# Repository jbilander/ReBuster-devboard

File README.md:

# ReBuster-devboard
A development board for ReBuster

***

<br />

<br />

<br />

***

***

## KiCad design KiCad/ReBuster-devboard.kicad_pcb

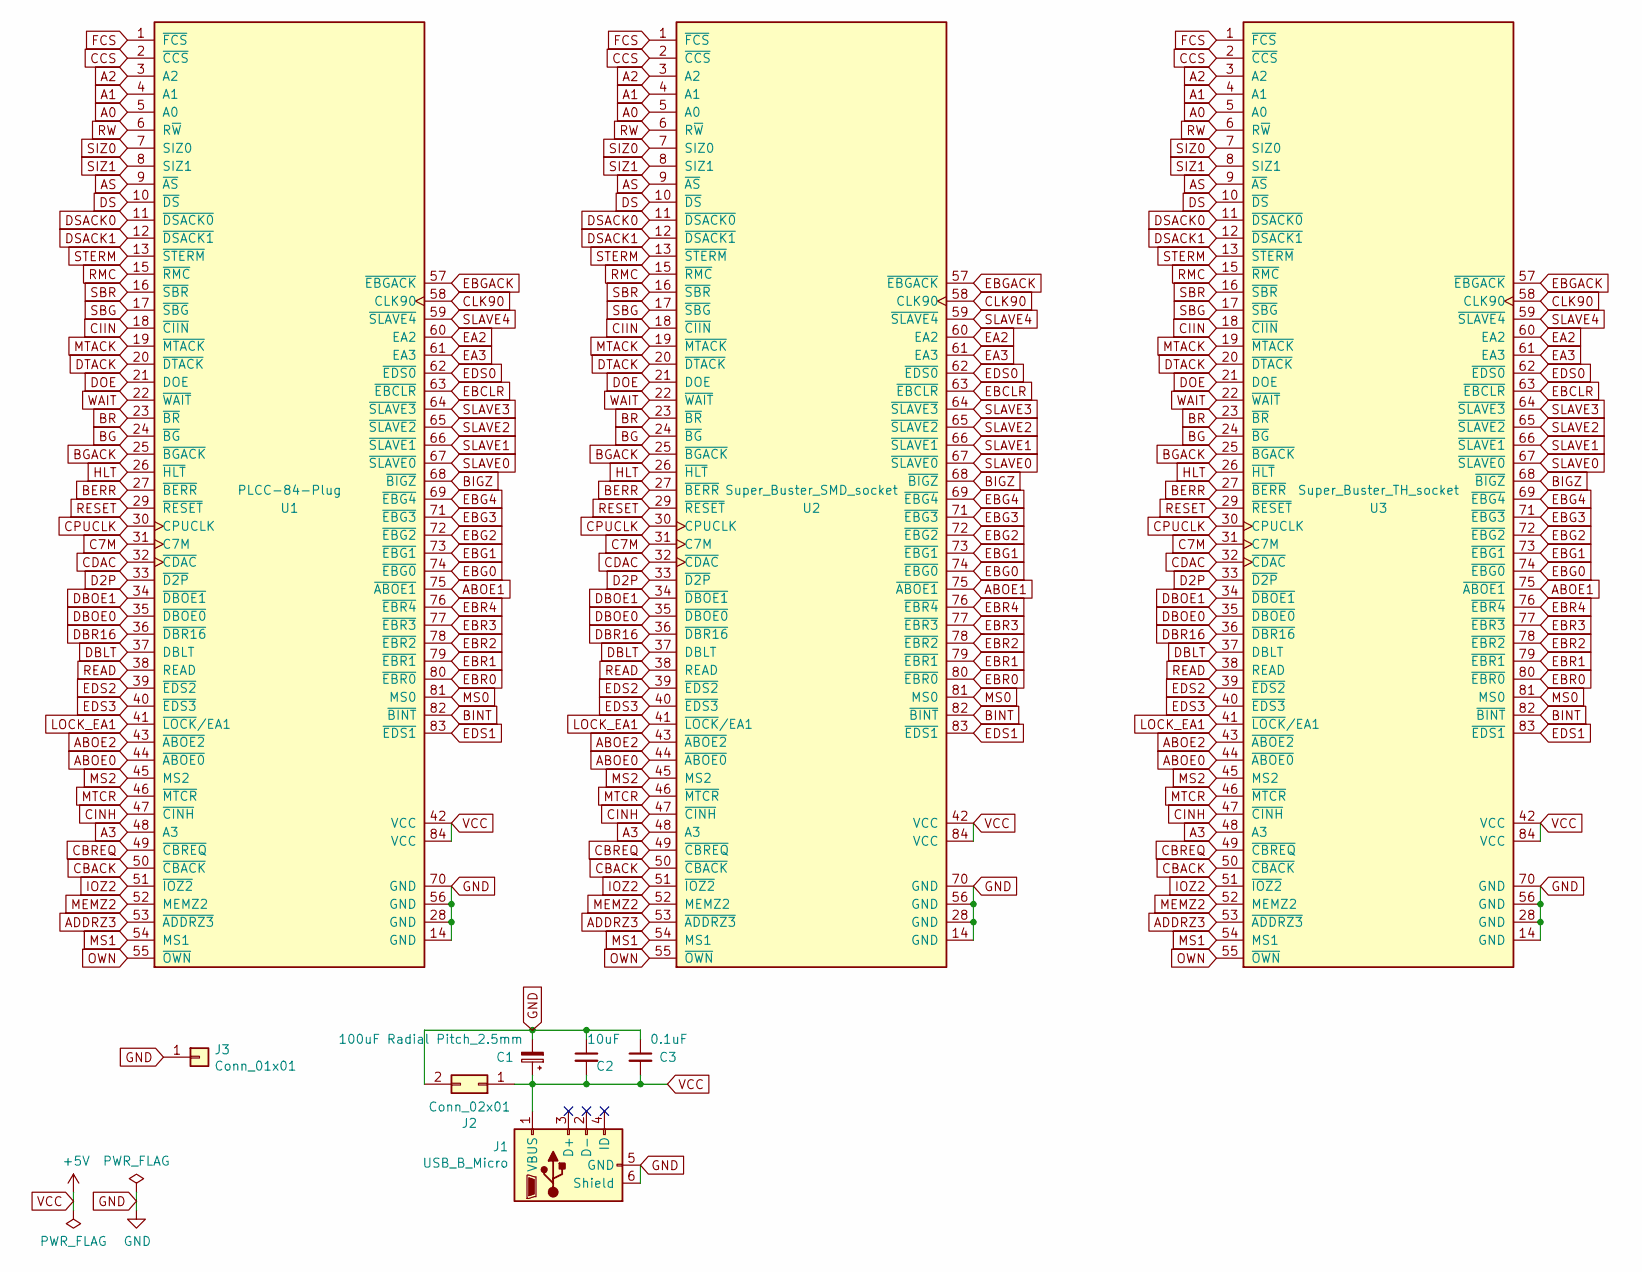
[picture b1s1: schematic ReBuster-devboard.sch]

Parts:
C1: 100uF Radial Pitch_2.5mm; CP_Radial_D5.0mm_P2.50mm
C2: 10uF; C_1206_3216Metric_Pad1.33x1.80mm_HandSolder
C3: 0.1uF; C_0805_2012Metric_Pad1.18x1.45mm_HandSolder
J1: USB_B_Micro; USB_Micro-B_Unknown_5s_SMT
J2: Conn_02x01; PinHeader_2x01_P2.54mm_Vertical
J3: Conn_01x01; MountingHole_3.2mm_M3_Pad_Via
U1: PLCC-84-Plug; PLCC-84_Plug_P1.27mm_mirrored
U2: Super_Buster_SMD_socket; PLCC-84_SMD-Socket_TH_modded
U3: Super_Buster_TH_socket; PLCC-84_THT-Socket

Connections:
A0: U1.5 (A0), U2.5 (A0), U3.5 (A0)
A1: U1.4 (A1), U2.4 (A1), U3.4 (A1)
A2: U1.3 (A2), U2.3 (A2), U3.3 (A2)
A3: U1.48 (A3), U2.48 (A3), U3.48 (A3)
ABOE0: U1.44 (~ABOE0), U2.44 (~ABOE0), U3.44 (~ABOE0)
ABOE1: U1.75 (~ABOE1), U2.75 (~ABOE1), U3.75 (~ABOE1)
ABOE2: U1.43 (~ABOE2), U2.43 (~ABOE2), U3.43 (~ABOE2)
ADDRZ3: U1.53 (~ADDRZ3), U2.53 (~ADDRZ3), U3.53 (~ADDRZ3)
AS: U1.9 (~AS), U2.9 (~AS), U3.9 (~AS)
BERR: U1.27 (~BERR), U2.27 (~BERR), U3.27 (~BERR)
BG: U1.24 (~BG), U2.24 (~BG), U3.24 (~BG)
BGACK: U1.25 (~BGACK), U2.25 (~BGACK), U3.25 (~BGACK)
BIGZ: U1.68 (~BIGZ), U2.68 (~BIGZ), U3.68 (~BIGZ)
BINT: U1.82 (~BINT), U2.82 (~BINT), U3.82 (~BINT)
BR: U1.23 (~BR), U2.23 (~BR), U3.23 (~BR)
C7M: U1.31 (C7M), U2.31 (C7M), U3.31 (C7M)
CBACK: U1.50 (~CBACK), U2.50 (~CBACK), U3.50 (~CBACK)
CBREQ: U1.49 (~CBREQ), U2.49 (~CBREQ), U3.49 (~CBREQ)
CCS: U1.2 (~CCS), U2.2 (~CCS), U3.2 (~CCS)
CDAC: U1.32 (~CDAC), U2.32 (~CDAC), U3.32 (~CDAC)
CIIN: U1.18 (~CIIN), U2.18 (~CIIN), U3.18 (~CIIN)
CINH: U1.47 (~CINH), U2.47 (~CINH), U3.47 (~CINH)
CLK90: U1.58 (CLK90), U2.58 (CLK90), U3.58 (CLK90)
CPUCLK: U1.30 (CPUCLK), U2.30 (CPUCLK), U3.30 (CPUCLK)
D2P: U1.33 (~D2P), U2.33 (~D2P), U3.33 (~D2P)
DBLT: U1.37 (DBLT), U2.37 (DBLT), U3.37 (DBLT)
DBOE0: U1.35 (~DBOE0), U2.35 (~DBOE0), U3.35 (~DBOE0)
DBOE1: U1.34 (~DBOE1), U2.34 (~DBOE1), U3.34 (~DBOE1)
DBR16: U1.36 (~DBR16), U2.36 (~DBR16), U3.36 (~DBR16)
DOE: U1.21 (DOE), U2.21 (DOE), U3.21 (DOE)
DS: U1.10 (~DS), U2.10 (~DS), U3.10 (~DS)
DSACK0: U1.11 (~DSACK0), U2.11 (~DSACK0), U3.11 (~DSACK0)
DSACK1: U1.12 (~DSACK1), U2.12 (~DSACK1), U3.12 (~DSACK1)
DTACK: U1.20 (~DTACK), U2.20 (~DTACK), U3.20 (~DTACK)
EA2: U1.60 (EA2), U2.60 (EA2), U3.60 (EA2)
EA3: U1.61 (EA3), U2.61 (EA3), U3.61 (EA3)
EBCLR: U1.63 (~EBCLR), U2.63 (~EBCLR), U3.63 (~EBCLR)
EBG0: U1.74 (~EBG0), U2.74 (~EBG0), U3.74 (~EBG0)
EBG1: U1.73 (~EBG1), U2.73 (~EBG1), U3.73 (~EBG1)
EBG2: U1.72 (~EBG2), U2.72 (~EBG2), U3.72 (~EBG2)
EBG3: U1.71 (~EBG3), U2.71 (~EBG3), U3.71 (~EBG3)
EBG4: U1.69 (~EBG4), U2.69 (~EBG4), U3.69 (~EBG4)
EBGACK: U1.57 (~EBGACK), U2.57 (~EBGACK), U3.57 (~EBGACK)
EBR0: U1.80 (~EBR0), U2.80 (~EBR0), U3.80 (~EBR0)
EBR1: U1.79 (~EBR1), U2.79 (~EBR1), U3.79 (~EBR1)
EBR2: U1.78 (~EBR2), U2.78 (~EBR2), U3.78 (~EBR2)
EBR3: U1.77 (~EBR3), U2.77 (~EBR3), U3.77 (~EBR3)
EBR4: U1.76 (~EBR4), U2.76 (~EBR4), U3.76 (~EBR4)
EDS0: U1.62 (~EDS0), U2.62 (~EDS0), U3.62 (~EDS0)
EDS1: U1.83 (~EDS1), U2.83 (~EDS1), U3.83 (~EDS1)
EDS2: U1.39 (~EDS2), U2.39 (~EDS2), U3.39 (~EDS2)
EDS3: U1.40 (~EDS3), U2.40 (~EDS3), U3.40 (~EDS3)
FCS: U1.1 (~FCS), U2.1 (~FCS), U3.1 (~FCS)
GND: C1.2, C2.1, C3.1, J1.5 (GND), J1.6 (Shield), J2.2, J3.1, U1.14 (GND), U1.28 (GND), U1.56 (GND), U1.70 (GND), U2.14 (GND), U2.28 (GND), U2.56 (GND), U2.70 (GND), U3.14 (GND), U3.28 (GND), U3.56 (GND), U3.70 (GND)
HLT: U1.26 (~HLT), U2.26 (~HLT), U3.26 (~HLT)
IOZ2: U1.51 (~IOZ2), U2.51 (~IOZ2), U3.51 (~IOZ2)
LOCK_EA1: U1.41 (~LOCK~/EA1), U2.41 (~LOCK~/EA1), U3.41 (~LOCK~/EA1)
MEMZ2: U1.52 (MEMZ2), U2.52 (MEMZ2), U3.52 (MEMZ2)
MS0: U1.81 (MS0), U2.81 (MS0), U3.81 (MS0)
MS1: U1.54 (MS1), U2.54 (MS1), U3.54 (MS1)
MS2: U1.45 (MS2), U2.45 (MS2), U3.45 (MS2)
MTACK: U1.19 (~MTACK), U2.19 (~MTACK), U3.19 (~MTACK)
MTCR: U1.46 (~MTCR), U2.46 (~MTCR), U3.46 (~MTCR)
OWN: U1.55 (~OWN), U2.55 (~OWN), U3.55 (~OWN)
READ: U1.38 (READ), U2.38 (READ), U3.38 (READ)
RESET: U1.29 (~RESET), U2.29 (~RESET), U3.29 (~RESET)
RMC: U1.15 (~RMC), U2.15 (~RMC), U3.15 (~RMC)
RW: U1.6 (R~W), U2.6 (R~W), U3.6 (R~W)
SBG: U1.17 (~SBG), U2.17 (~SBG), U3.17 (~SBG)
SBR: U1.16 (~SBR), U2.16 (~SBR), U3.16 (~SBR)
SIZ0: U1.7 (SIZ0), U2.7 (SIZ0), U3.7 (SIZ0)
SIZ1: U1.8 (SIZ1), U2.8 (SIZ1), U3.8 (SIZ1)
SLAVE0: U1.67 (~SLAVE0), U2.67 (~SLAVE0), U3.67 (~SLAVE0)
SLAVE1: U1.66 (~SLAVE1), U2.66 (~SLAVE1), U3.66 (~SLAVE1)
SLAVE2: U1.65 (~SLAVE2), U2.65 (~SLAVE2), U3.65 (~SLAVE2)
SLAVE3: U1.64 (~SLAVE3), U2.64 (~SLAVE3), U3.64 (~SLAVE3)
SLAVE4: U1.59 (~SLAVE4), U2.59 (~SLAVE4), U3.59 (~SLAVE4)
STERM: U1.13 (~STERM), U2.13 (~STERM), U3.13 (~STERM)
VCC: C1.1, C2.2, C3.2, J1.1 (VBUS), J2.1, U1.42 (VCC), U1.84 (VCC), U2.42 (VCC), U2.84 (VCC), U3.42 (VCC), U3.84 (VCC)
WAIT: U1.22 (~WAIT), U2.22 (~WAIT), U3.22 (~WAIT)

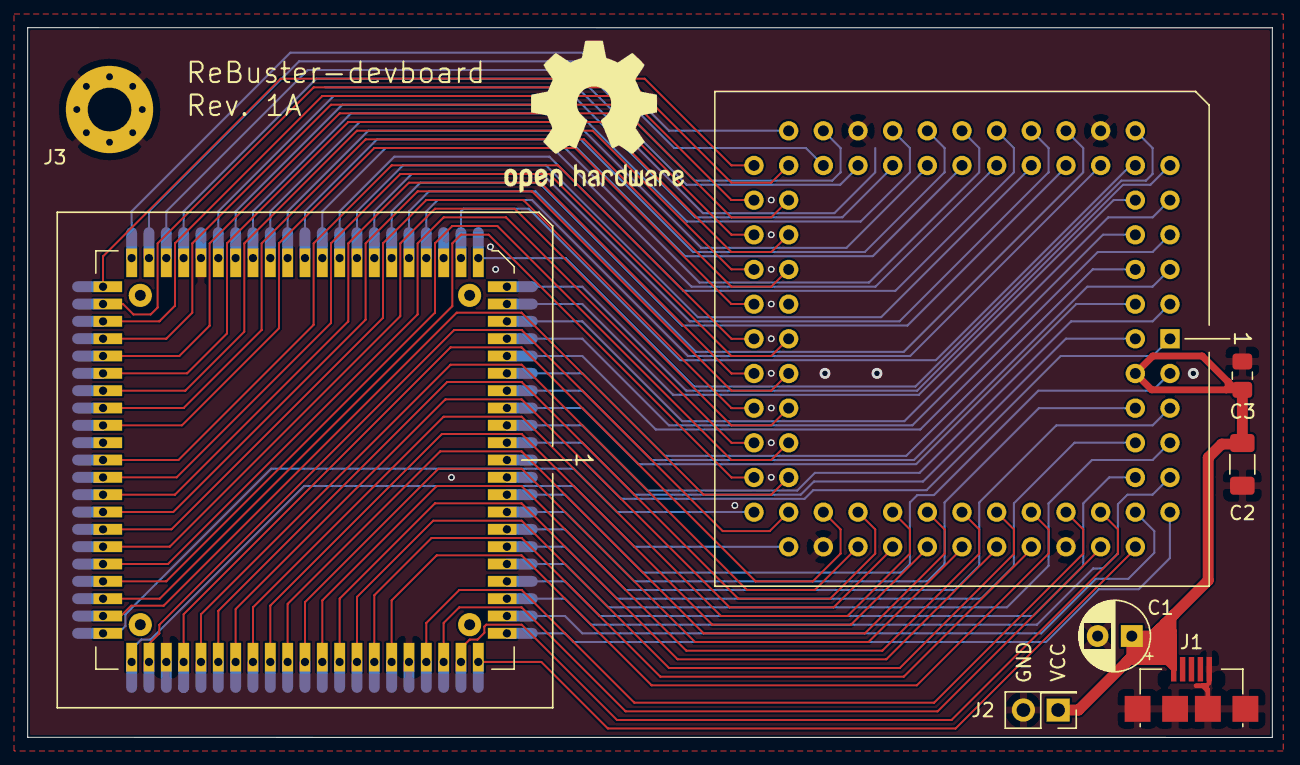
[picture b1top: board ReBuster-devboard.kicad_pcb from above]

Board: 4 copper layers, 91.2 x 52.0 mm, 9 parts (1 on the bottom side), 80 nets.

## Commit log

2024-11-21 Add license
2024-11-23 Add footprints
2024-11-23 Add KiCad source files
2024-11-23 Add screenshot image
2024-12-25 add image
2025-02-02 Add images
